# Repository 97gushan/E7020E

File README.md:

# E7020E
Repository for the course Embedded System Design

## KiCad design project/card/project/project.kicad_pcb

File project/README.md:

# Project in Embedded System

Albin Martinsson \
Gustav Hansson

## Project Idea

Parking sensor using an ultra sound sensor for measuring distance.

## Dependencies

- Rust 1.40, or later.

``` console
        > rustup update
        > rustup target add thumbv7em-none-eabihf
```

- For programming (flashing) and debugging
  - `openocd` debug host, (install using your package manager).

    For `Ubuntu` and `OSX`: use `source [find interface/stlink-v2-1.cfg]` in the `openocd.cfg` and the `.vscode/launch.json` if VSCode is used.

    For other operating systems use `source [find interface/stlink.cfg]`

  - `arm-none-eabi` tool-chain (install using your package manager).

- Configure your Nucleo programmer, [Datasheet with how to configure](https://www.st.com/content/ccc/resource/technical/document/user_manual/98/2e/fa/4b/e0/82/43/b7/DM00105823.pdf/files/DM00105823.pdf/jcr:content/translations/en.DM00105823.pdf)

## Run

- Connect the SWD pins from the Nucleo to the respective pins on the card
- run `openocd -f openocd.cfg` from the project folder, the same that this file is in.
- run `cargo run`.

Tried on Ubuntu 19 and Arch

## Assumptions (brasklapp)

We could not get the distance sensor to work so we did the following work around.

We used the value that the potentiometer returns to act as the distance to the object, the higher the value the nearer the object is and vice versa. 
Based on the limited number of timers, 4, the MCU supports we defined three intervals. We could only use three timers to define the frequency because on timer has to be used to turn the piezo element on and off. Far away, near and crash. Each of the intervals correspends to a frequncy the buzzer beeps and also what the OLED screen prints out. 

## Specs

### Purpose

Enables a safer way to park your car.

### Limitations

Using only one cheap distance sensor the distance and area covered by the sensor is suboptimal. Smaller obstacles coming in at an angle could be missed by the sensor and thus the driver should always look where he drives. It should be used as an aid, not a guide.

### Behaviour

The distance is measured with a ultra sound and a speaker that warns the driver of an approaching obstacle. The parking sensor can be turned on and off by a button and the distance is broadcasted to a user via the radio.

### Safety

This system should not be blindly relied on and the driver should always look where he drives. The producer takes no responsibility for damage to objects or persons.

### Liveness

The system should measure distance in real time and based on a threshold make a warning sound. This sound can not be delayed more than 200ms.

### Robustness

To prevent malformed packages we poll data from the sensor during a short interval on around 100 ms. During this interval we can check to see that the measured data is reliable by comparing it to the rest of the measured data during that interval. Thus we can know if a package is malformed or if a distance is measured wrongly.

### Security

The system uses very non personal data thus encryption is not needed.

## Components

- Ultrasonic distance sensor
- OLED screen
- Speaker
- LED
- Button
- Antenna

## Ultrasonic distance sensor

Here we will provide some links to potential components to order, each component will have a short description of specs.

### [4019 - US-100](https://www.elfa.se/en/us-100-ultrasonic-distance-sensor-5v-adafruit-4019/p/30139213?q=Ultrasonic+distance+sensor&pos=4&origPos=4&origPageSize=10&track=true)

- Distance range: 0.02...4.5m
- 15 degree angle
- 67,10 SEK
- 3-5V DC
- 2mA (Would depend on the voltage suplied..?)

## [OLED screen](https://cdon.se/hem-tradgard/oled-display-0-96-tum-vit-128x64-pixlar-ssd1306-spi-p50506639)

## [Speaker](https://www.elfa.se/en/electromechanical-buzzer-70db-3khz-4v-pcb-pins-rnd-components-rnd-430-00022/p/30160669?q=*&pos=3&origPos=10&origPageSize=10&track=true)

## Headers

### [2 pin male](https://se.rs-online.com/web/p/pcb-headers/2518086/)

### [5 pin female](https://www.elfa.se/en/straight-female-pcb-receptacle-through-hole-rows-contacts-54mm-pitch-rnd-connect-rnd-205-00645/p/30093665?q=pcb+headers&pos=1&origPos=388&origPageSize=10&track=true)

### [6 pin male](https://www.elfa.se/en/straight-male-pcb-header-through-hole-rows-contacts-54mm-pitch-rnd-connect-rnd-205-00627/p/30093647?q=pcb+headers&pos=9&origPos=868&origPageSize=10&track=true)

### [7 pin female](https://www.elfa.se/en/straight-female-pcb-receptacle-through-hole-rows-contacts-54mm-pitch-rnd-connect-rnd-205-00647/p/30093667?q=pcb+headers&pos=2&origPos=397&origPageSize=10&track=true)

## [USB-connector](https://se.rs-online.com/web/p/micro-usb-connectors/1225099/)

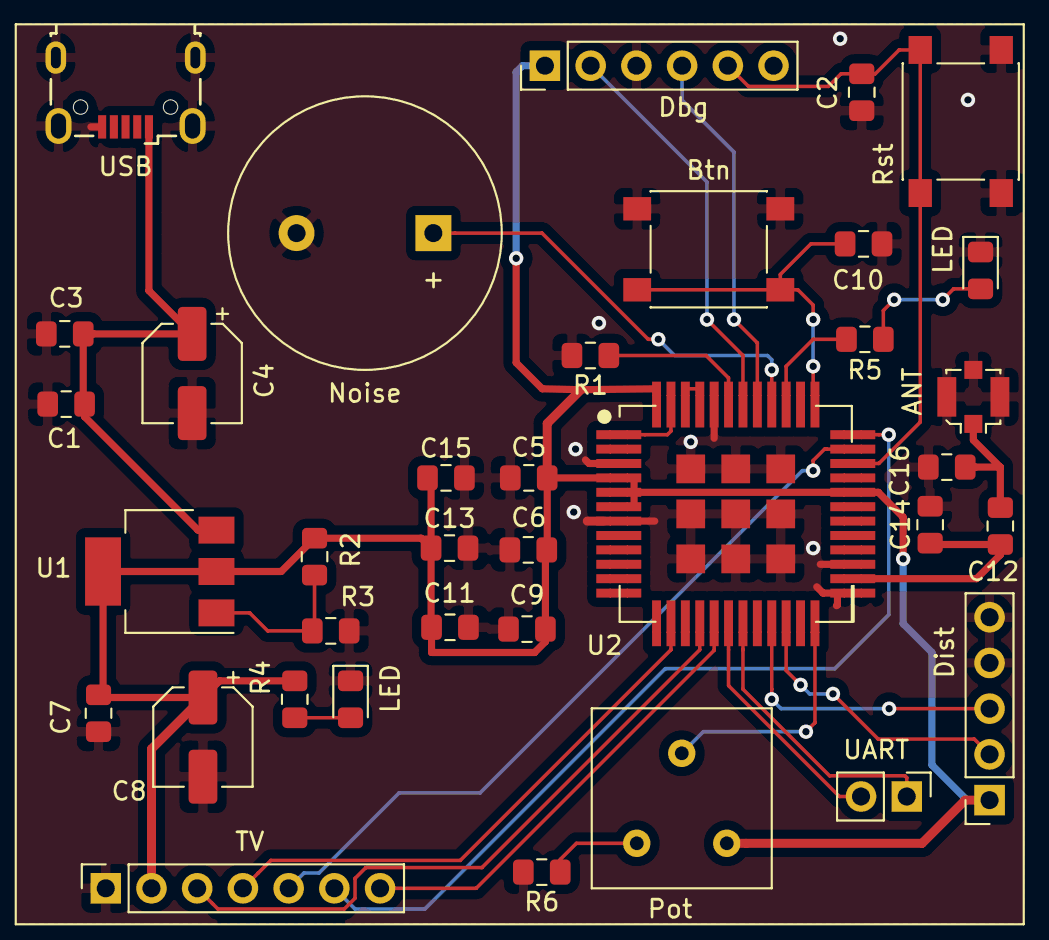
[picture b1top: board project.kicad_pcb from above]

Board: 2 copper layers, 36 parts (0 on the bottom side), 28 nets.

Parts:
ANT: Conn_Coaxial; U.FL_Molex_MCRF_73412-0110_Vertical
Btn: SW_Push; SW_Push_1P1T_NO_6x6mm_H9.5mm
C1, C3, C7: 100n; C_0805_2012Metric_Pad1.15x1.40mm_HandSolder
C2, C5, C9, C10: 0.1u; C_0805_2012Metric_Pad1.15x1.40mm_HandSolder
C4, C8: 10u; CP_Elec_5x4.5
C6, C13: 10u; C_0805_2012Metric_Pad1.15x1.40mm_HandSolder
C11, C15: 1u; C_0805_2012Metric_Pad1.15x1.40mm_HandSolder
C12: 100p; C_0805_2012Metric_Pad1.15x1.40mm_HandSolder
C14, C16: DNP; C_0805_2012Metric_Pad1.15x1.40mm_HandSolder
Dbg: Conn_01x06_Male; PinHeader_1x06_P2.54mm_Vertical
Dist: Conn_01x05_Female; PinSocket_1x05_P2.54mm_Vertical
LED: LED; LED_0805_2012Metric_Pad1.15x1.40mm_HandSolder
LED#2: LED; LED_0805_2012Metric_Pad1.15x1.40mm_HandSolder
Noise: Speaker_Crystal; Buzzer_15x7.5RM7.6
Pot: R_POT; Potetio
R1, R6: 10k; R_0805_2012Metric_Pad1.15x1.40mm_HandSolder
R2: 1k; R_0805_2012Metric_Pad1.15x1.40mm_HandSolder
R3: 1.65k; R_0805_2012Metric_Pad1.15x1.40mm_HandSolder
R4: 680; R_0805_2012Metric_Pad1.15x1.40mm_HandSolder
R5: 220; R_0805_2012Metric_Pad1.15x1.40mm_HandSolder
Rst: SW_Push; SW_Push_1P1T_NO_6x6mm_H9.5mm
TV: Conn_01x07_Female; PinSocket_1x07_P2.54mm_Vertical
U1: LM1117ADJ; SOT-223
U2: CMWX1ZZABZ-078; CMWX1ZZABZ
UART: Conn_01x02_Male; PinHeader_1x02_P2.54mm_Vertical
USB: USB_OTG; USB_Micro-B_Wuerth_629105150521

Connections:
+3V3: C5.1, C6.1, C7.1, C8.1, C9.1, C11.1, C13.1, C15.1, Dbg.1, Dist.1, Pot.1, R2.1, R4.2, TV.2, U1.2, U1.4, U2.4, U2.5, U2.6, U2.32, U2.48
+5V: C1.1, C3.1, C4.1, U1.3, USB.1
/Btn: Btn.1, C10.2, U2.37
/DataCom: TV.6, U2.36
/LED: R5.2, U2.39
/NSS: TV.7, U2.17
/POT: Pot.2, U2.24
/Piezo: Noise.1, U2.40
/Reset: TV.5, U2.35
/echo: Dist.3, U2.21
/trig: Dist.2, U2.22
GND: ANT.2, Btn.2, C1.2, C2.1, C3.2, C4.2, C5.2, C6.2, C7.2, C8.2, C9.2, C10.1, C11.2, C13.2, C14.2, C15.2, C16.2, Dbg.3, Dist.4, Dist.5, LED.1, LED#2.1, Noise.2, R1.2, R3.2, R6.2, Rst.1, TV.1, U2.3, U2.7, U2.25, U2.27, U2.44, U2.49, U2.50, U2.51, U2.52, U2.53, U2.54, U2.55, U2.56, U2.57, USB.5, USB.6
unnamed: C2.2, Dbg.5, Rst.2, U2.34
unnamed: ANT.1, C12.1, C16.1
unnamed: C12.2, C14.1, U2.26
unnamed: LED#2.2, R5.1
unnamed: LED.2, R4.1
unnamed: Dbg.2, U2.42
unnamed: Dbg.4, U2.41
unnamed: U2.19, UART.1
unnamed: U2.18, UART.2
unnamed: TV.3, U2.16
unnamed: TV.4, U2.14
unnamed: R1.1, U2.43
unnamed: R2.2, R3.1, U1.1
unnamed: Pot.3, R6.1
unnamed: U2.1, U2.47
unnamed: U2.45, U2.46

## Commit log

2020-01-22 began work on lab 1
2020-01-27 lab 1
2020-01-27 presentation
2020-01-30 Added components in the project readme
2020-01-30 Reversed order of headers because stupid
2020-02-03 lab 2
2020-02-03 began work on project card
2020-02-05 schematic design v1
2020-02-05 began work with footprints
2020-02-07 add all footprints
2020-02-10 Added components to readme
2020-02-10 Fixed headers
2020-02-10 Added the correct distance sensor
2020-02-10 layout etc
2020-02-11 fix routes and generate gerber
2020-02-13 poooootentiometer addeded
2020-02-13 v1.0
2020-02-13 update bom
2020-02-13 update antenna text
2020-03-09 basic project with button events and led output
2020-03-18 buzzer
2020-03-19 peizo buzzer
2020-03-20 workworkwork
2020-03-20 pot work!!!!
2020-03-20 tv work!!!
2020-03-23 fix potentiometer
2020-03-23 cleanup and remove example
2020-04-03 Final commit with changes to pot, screen buzzer
2020-04-03 added assumptions to readme
